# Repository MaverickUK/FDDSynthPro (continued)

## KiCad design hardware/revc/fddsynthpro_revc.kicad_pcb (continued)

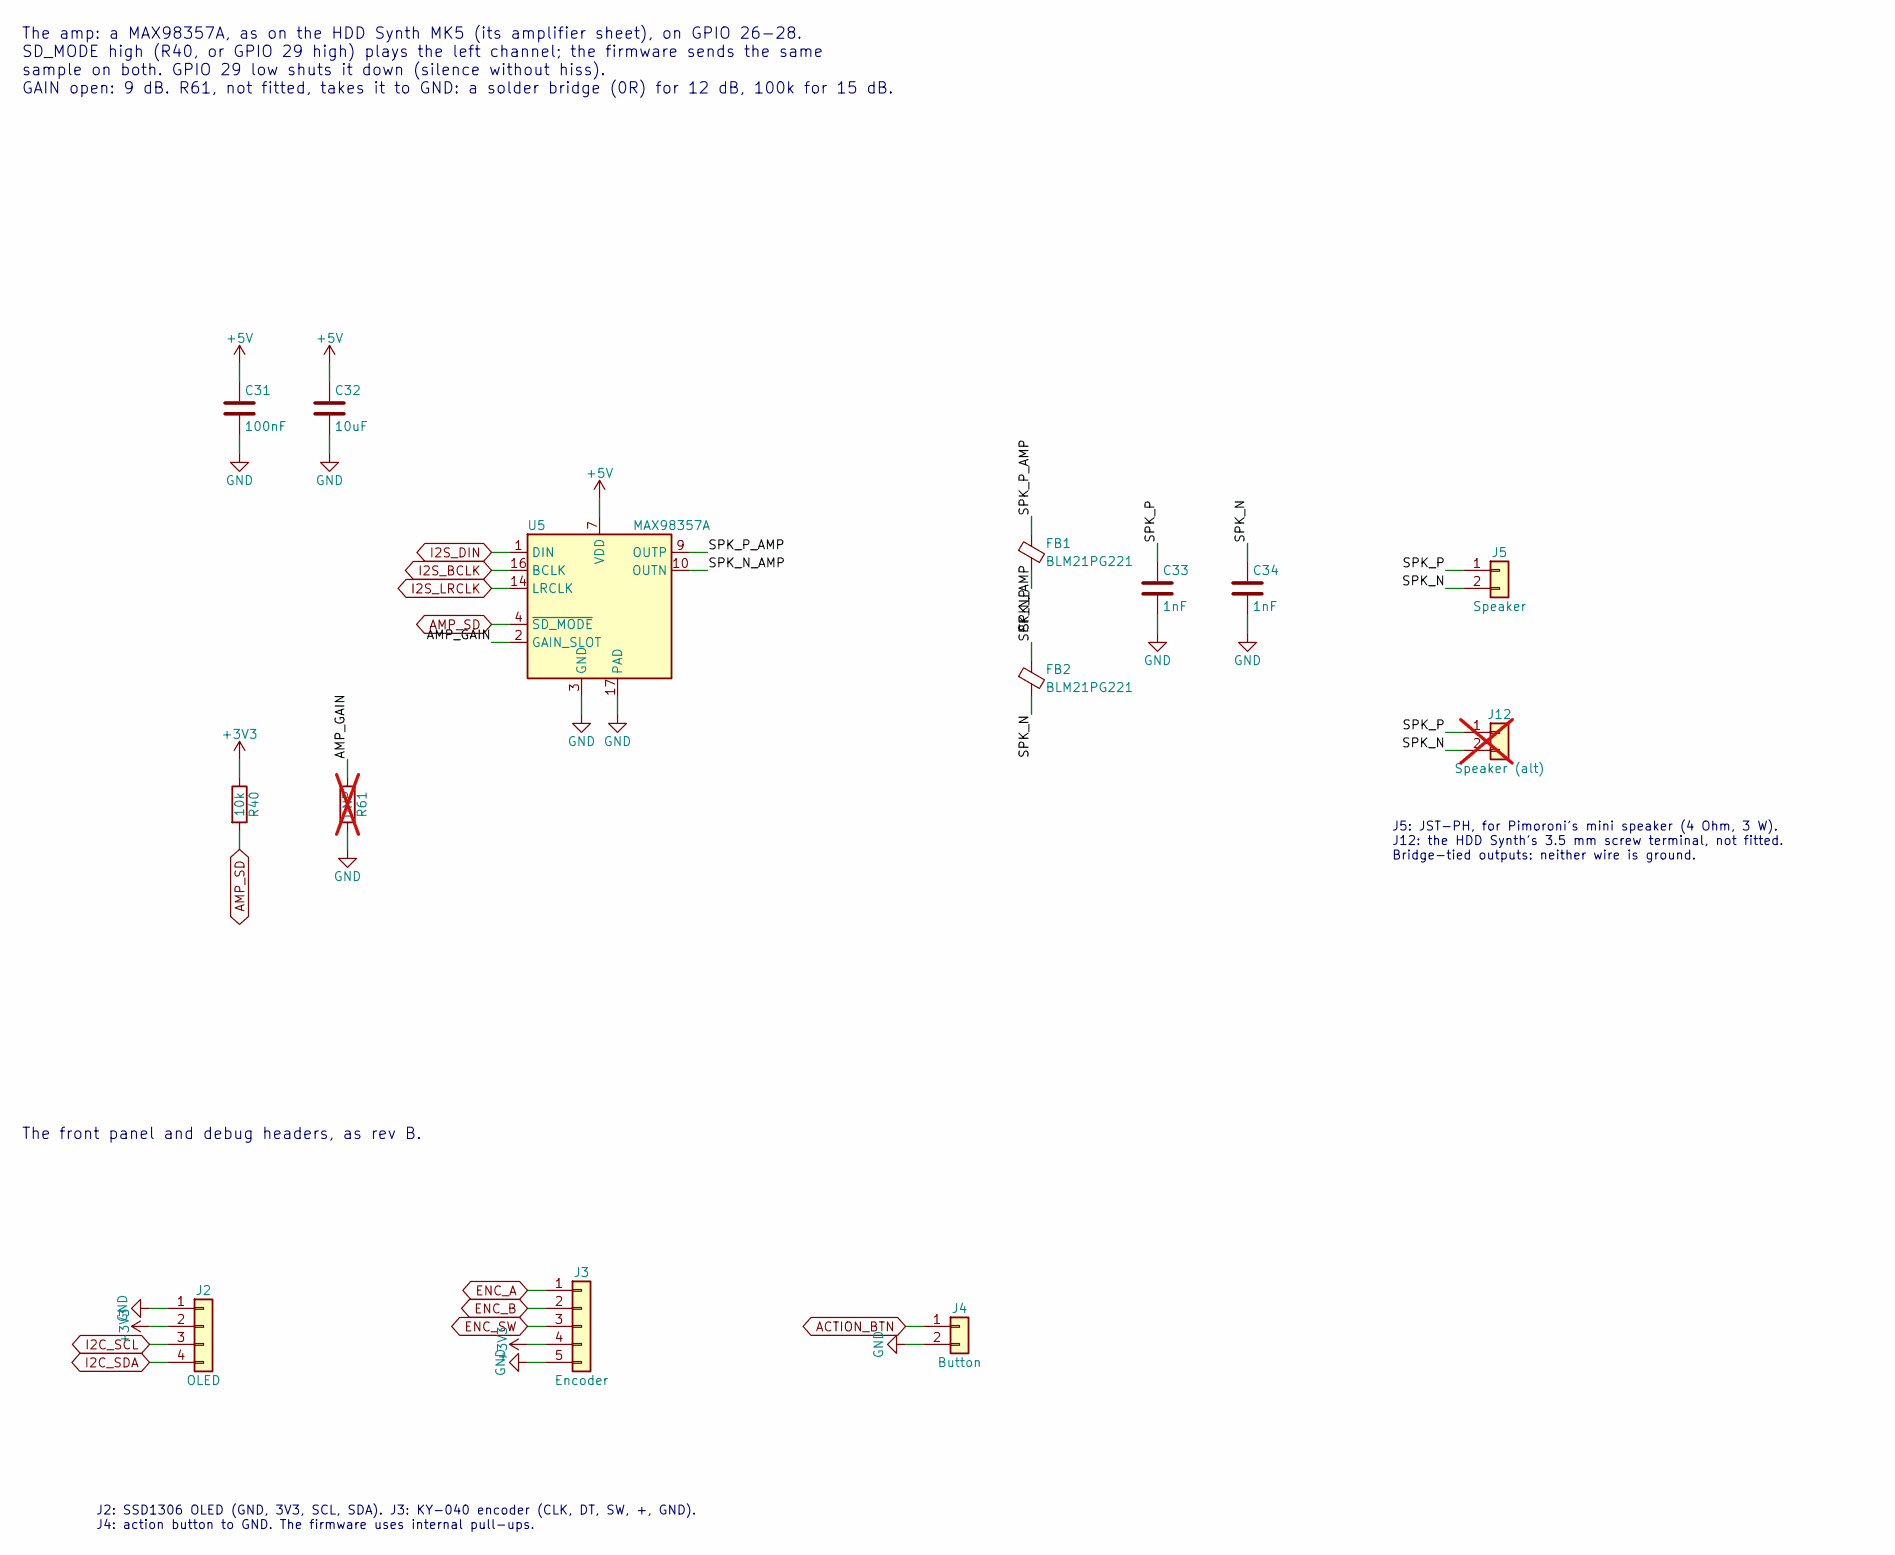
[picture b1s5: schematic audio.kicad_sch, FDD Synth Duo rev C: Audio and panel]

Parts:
C31: 100nF; C_0402_1005Metric; LCSC Part Number C1525
C32: 10uF; C_0805_2012Metric; LCSC Part Number C15850
C33, C34: 1nF; C_0603_1608Metric; LCSC Part Number C1588
FB1, FB2: BLM21PG221; L_0805_2012Metric; LCSC Part Number C85840
J2: OLED; PinHeader_1x04_P2.54mm_Vertical; LCSC Part Number C124378
J3: Encoder; PinHeader_1x05_P2.54mm_Vertical; LCSC Part Number C124379
J4: Button; PinHeader_1x02_P2.54mm_Vertical; LCSC Part Number C124375
J5: Speaker; JST_PH_B2B-PH-K_1x02_P2.00mm_Vertical; MPN JST B2B-PH-K-S; LCSC Part Number C131337
J12: Speaker (alt); TerminalBlock_Phoenix_PT-1,5-2-3.5-H_1x02_P3.50mm_Horizontal; MPN KF350-3.5-2P; LCSC Part Number C474892; not fitted
R40: 10k; R_0402_1005Metric; LCSC Part Number C25744
R61: DNP; R_0402_1005Metric; not fitted
U5: MAX98357A; TQFN-16-1EP_3x3mm_P0.5mm_EP1.23x1.23mm_ThermalVias; LCSC Part Number C910544

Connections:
+3V3: J2.2, J3.4, R40.1; also elsewhere on the board
+5V: C31.1, C32.1, U5.7 (VDD), U5.8 (VDD); also elsewhere on the board
/Audio and panel/AMP_GAIN: R61.1, U5.2 (GAIN_SLOT)
/Audio and panel/SPK_N: C34.1, FB2.2, J5.2, J12.2
/Audio and panel/SPK_N_AMP: FB2.1, U5.10 (OUTN)
/Audio and panel/SPK_P: C33.1, FB1.2, J5.1, J12.1
/Audio and panel/SPK_P_AMP: FB1.1, U5.9 (OUTP)
ACTION_BTN: J4.1; also elsewhere on the board
AMP_SD: R40.2, U5.4 (~SD_MODE); also elsewhere on the board
ENC_A: J3.1; also elsewhere on the board
ENC_B: J3.2; also elsewhere on the board
ENC_SW: J3.3; also elsewhere on the board
GND: C31.2, C32.2, C33.2, C34.2, J2.1, J3.5, J4.2, R61.2, U5.3 (GND), U5.11 (GND), U5.15 (GND), U5.17 (PAD); also elsewhere on the board
I2C_SCL: J2.3; also elsewhere on the board
I2C_SDA: J2.4; also elsewhere on the board
I2S_BCLK: U5.16 (BCLK); also elsewhere on the board
I2S_DIN: U5.1 (DIN); also elsewhere on the board
I2S_LRCLK: U5.14 (LRCLK); also elsewhere on the board

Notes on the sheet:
The amp: a MAX98357A, as on the HDD Synth MK5 (its amplifier sheet), on GPIO 26-28. SD_MODE high (R40, or GPIO 29 high) plays the left channel; the firmware sends the same sample on both. GPIO 29 low shuts it down (silence without hiss). GAIN open: 9 dB. R61, not fitted, takes it to GND: a solder b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
J5: JST-PH, for Pimoroni's mini speaker (4 Ohm, 3 W). J12: the HDD Synth's 3.5 mm screw terminal, not fitted. Bridge-tied outputs: neither wire is ground.
The front panel and debug headers, as rev B.
J2: SSD1306 OLED (GND, 3V3, SCL, SDA). J3: KY-040 encoder (CLK, DT, SW, +, GND). J4: action button to GND. The firmware uses internal pull-ups.

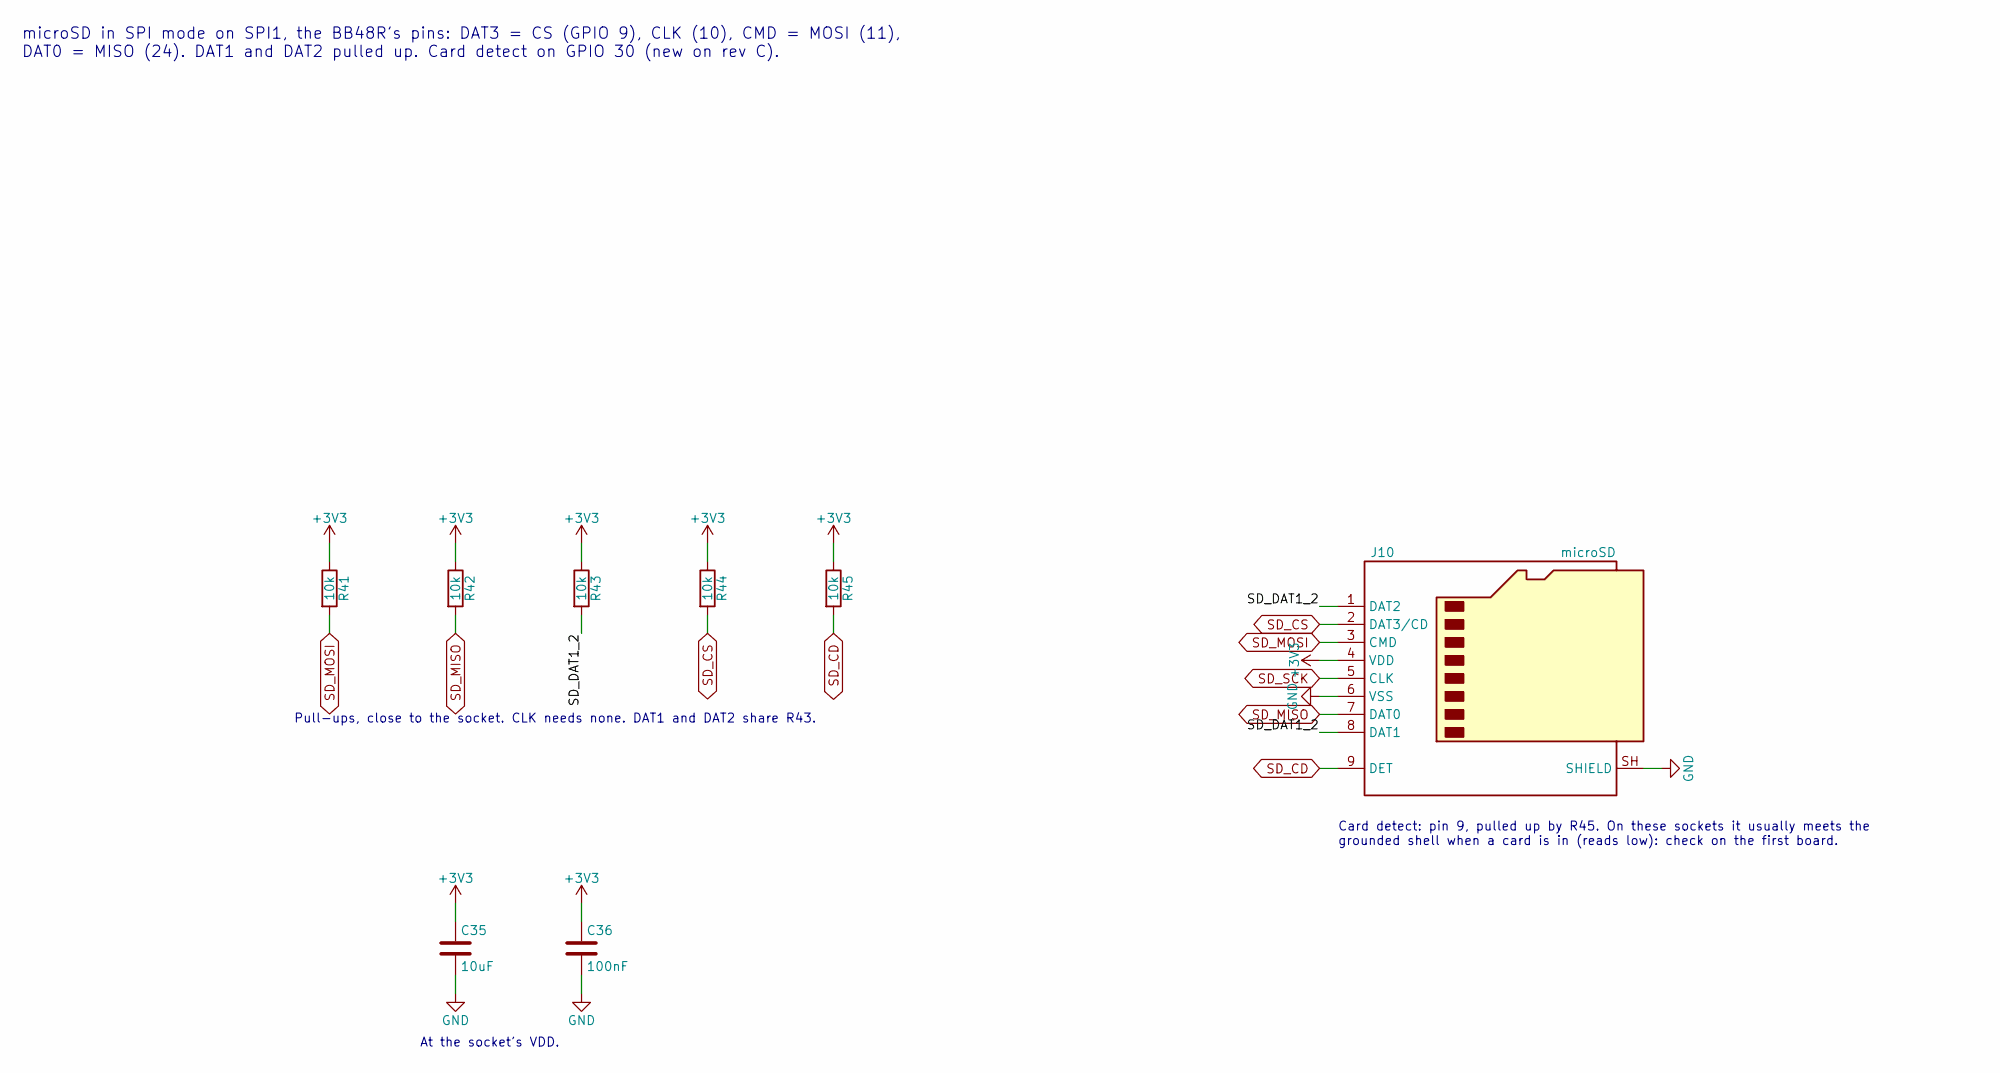
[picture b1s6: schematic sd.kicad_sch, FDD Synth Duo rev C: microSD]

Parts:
C35: 10uF; C_0805_2012Metric; LCSC Part Number C15850
C36: 100nF; C_0402_1005Metric; LCSC Part Number C1525
J10: microSD; microSD_TF-PUSH; MPN TF PUSH (generic push-push); LCSC Part Number C393941
R41, R42, R43, R44, R45: 10k; R_0402_1005Metric; LCSC Part Number C25744

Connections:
+3V3: C35.1, C36.1, J10.4 (VDD), R41.1, R42.1, R43.1, R44.1, R45.1; also elsewhere on the board
/microSD/SD_DAT1_2: J10.1 (DAT2), J10.8 (DAT1), R43.2
GND: C35.2, C36.2, J10.6 (VSS), J10.SH (SHIELD); also elsewhere on the board
SD_CD: J10.9 (DET), R45.2; also elsewhere on the board
SD_CS: J10.2 (DAT3/CD), R44.2; also elsewhere on the board
SD_MISO: J10.7 (DAT0), R42.2; also elsewhere on the board
SD_MOSI: J10.3 (CMD), R41.2; also elsewhere on the board
SD_SCK: J10.5 (CLK); also elsewhere on the board

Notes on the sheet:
microSD in SPI mode on SPI1, the BB48R's pins: DAT3 = CS (GPIO 9), CLK (10), CMD = MOSI (11), DAT0 = MISO (24). DAT1 and DAT2 pulled up. Card detect on GPIO 30 (new on rev C).
Card detect: pin 9, pulled up by R45. On these sockets it usually meets the grounded shell when a card is in (reads low): check on the first board.
Pull-ups, close to the socket. CLK needs none. DAT1 and DAT2 share R43.
At the socket's VDD.

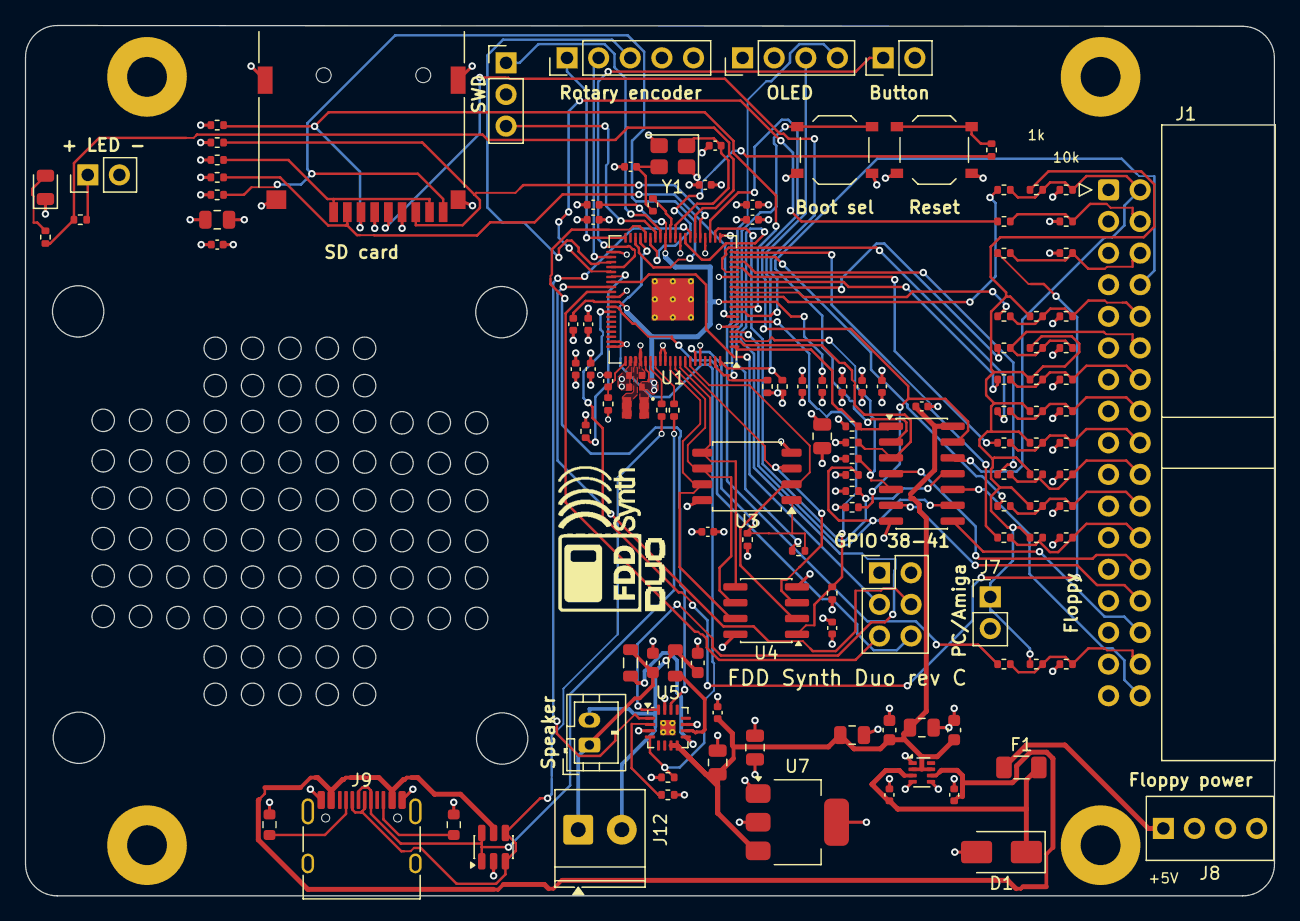
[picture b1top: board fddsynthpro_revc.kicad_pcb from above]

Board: 4 copper layers, 100.3 x 69.9 mm, 134 parts (1 on the bottom side), 95 nets.

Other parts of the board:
LOGO1: FDDSynthDuo_Logo
LOGO2: DontCopyThatFloppy

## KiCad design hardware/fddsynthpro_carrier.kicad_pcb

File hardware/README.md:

# FDD Synth Duo carrier board

A KiCad 10 project for the board the Olimex RP2350-PICO2-BB48R plugs onto: the SN7407, the floppy header, the input pull-ups, and headers for the front panel and the amp. It's the circuit in [docs/wiring.md](../docs/wiring.md), with the pin map in [src/config.h](../src/config.h).

**Rev B** has the HDD Synth MK5's outline, mounting holes and speaker grille, so it fits the same case. It's built for JLCPCB assembly: they fit everything but the BB48R, which is marked DNP (do not populate) and plugged in by hand.

## The board

- **The outline**, 100.3 × 69.9 mm, is copied from the HDD Synth MK5's own PCB ([mk5_outline.py](mk5_outline.py)). That includes its speaker grille, the four 4.1 mm speaker-mounting holes, and the four M3 mounting holes (plated and grounded, as on the MK5). No copper goes under the speaker.
- **The speaker** is Pimoroni's mini speaker (4 Ω, 3 W, JST-PH): 40 × 40 × 20 mm, M2.5 holes 32.5 mm apart. On the MK5's holes (34 mm apart, 4.1 mm across) it covers x 1.3–41.3 mm; the nearest part (the header column) starts 2.3 mm beyond its frame. The MK5's holes are 0.75 mm wider-spaced than the speaker's on each side, which an M2.5 screw in a 4.1 mm hole just takes.
- **The BB48R stands upright, turned round:** its USB-C socket is at the bottom edge and its microSD slot (on its underside) at the top edge. Turned this way, its EXT1 row, which carries every floppy signal, faces J1, and its EXT2 row, with the amp and encoder pins, faces the headers. The pin map is unchanged. The case may need openings for both; the HDD Synth's USB-C sits on the right edge instead.
- **J1, the floppy box header,** is on the right, between the right-hand mounting holes, turned round so its signal row faces the BB48R.
- **The pull-ups:** the twenty 0402 resistors stand between the BB48R and J1, one 10 kΩ and one 1 kΩ on each input's row. Each input runs straight along its row through both, and their other ends drop through vias to two buses on the underside.
- **The SN7407 (U2)** and its 100 nF capacitor sit below the pull-ups, beside GP4–7, its inputs.
- **The headers** form one column on the left, between the speaker and the BB48R, labelled pin by pin and titled beside each group.
- **Tracks:** 0.3 mm everywhere (ground, 3.3 V and VBUS all cross under the BB48R, between its pins, where nothing wider fits), 0.2 mm clearance, 0.6/0.3 mm vias, and ground poured on both sides. A 0.3 mm track carries about 1 A.

## The circuit

| Ref | Part | LCSC | Fitted by | Notes |
|---|---|---|---|---|
| U1 | Olimex RP2350-PICO2-BB48R | — | You (DNP) | Two 1×27 female headers are best: they give the microSD card room underneath and let you swap the board |
| U2 | SN7407DR, SOIC-14 | C40481 | JLCPCB | The five outputs: GPIO → A, Y → floppy header. Powered from VBUS; the sixth gate's input is tied to GND (see the pin 2 rework below) |
| C1 | 100 nF, 0603 | C14663 | JLCPCB | U2's decoupling |
| R1–R10 | 10 kΩ, 0402 | C25744 | JLCPCB | Pull-ups on the ten inputs to 3.3 V: right for the FeatherWing host |
| R11–R20 | 1 kΩ, 0402 | C11702 | JLCPCB | Pull-ups to PC_TERM, which J7 joins to 3.3 V |
| J1 | 2×17 box header, straight | C9042 | JLCPCB | The floppy cable. Odd pins to ground; 4 and 6 unconnected |
| J2 | 1×4 header: GND, 3V3, SCL, SDA | C124378 | JLCPCB | SSD1306 OLED. The BB48R's own Qwiic socket carries the same I2C1 pins |
| J3 | 1×5 header: CLK, DT, SW, +, GND | C124379 | JLCPCB | Rotary encoder. A KY-040 module plugs straight in |
| J4 | 1×2 header | C124375 | JLCPCB | The action button, to GND |
| J5 | 1×7 header: LRC, BCLK, DIN, GAIN, SD, GND, Vin | C492406 | JLCPCB | Adafruit MAX98357A, in its own pin order. GAIN and SD unconnected |
| J6 | 1×3 header: TX, RX, GND | C124376 | JLCPCB | Debug UART on GP0/GP1 |
| J7 | 1×2 header and a jumper | C124375 | JLCPCB (the jumper cap: you) | **The termination switch:** off for the FeatherWing host (10 kΩ); on for a real PC (the 1 kΩ in parallel: 909 Ω) |

The BB48R's own pins are left alone: GP8 (PSRAM select), GP9–11 and GP24 (the microSD slot), and GP25 (the LED).

**Rework for Shugart and Amiga hosts:** rev B only reads floppy pin 2 (a PC's density select). Shugart and Amiga hosts want the drive to drive it, with DISK CHANGE. Lift U2 pin 13 from ground and wire it to GP23 (EXT1-27), wire U2 pin 12 to J1 pin 2, and set `pin02=chg` ([docs/wiring.md](../docs/wiring.md#pin-2-for-shugart-and-amiga-hosts-a-rework)). A rev C should route the sixth gate that way from the start.

Rev A had a socketed DIP SN7407 and solder jumpers (JP1–JP5) to bypass it for the `direct` builds. A soldered SOIC can't be taken out, so rev B always has its SN7407. The `direct` builds remain for hand-wired rigs.

## Ordering from JLCPCB

`hardware/build.sh` writes everything:

- `fddsynthpro_carrier_fab.zip`: the Gerbers and drill files. Upload it as it is: two layers, 1.6 mm, HASL or ENIG.
- `jlc/bom.csv` and `jlc/positions.csv`: the assembly BOM and placement (CPL) in JLCPCB's format, without U1 (DNP). KiCad's Fabrication Toolkit plugin writes its own set to `production/` (with "Exclude DNP" on, in `fabrication-toolkit-options.json`); either set works. Choose top-side assembly. J1–J7 are through-hole, so they need Standard PCBA rather than Economic.

Each part's LCSC number is in a field named **LCSC Part Number**, as on the HDD Synth, so KiCad's Fabrication Toolkit plugin fills its BOM from the schematic too; it also leaves U1 out when "Exclude DNP" is set. The pin headers are Ckmtw's `B-2100S0xP-A110`, as on the HDD Synth; Ckmtw makes no 1×7, so J5 is XFCN's `PZ254V-11-07P`.

**Before paying, check JLCPCB's placement preview.** Their footprints don't always share KiCad's zero angle, SOICs especially, so make sure U2's pin-1 dot matches the board's marking. Rotate it in the preview if not.

**Extended parts:** U2, J1 and the five different pin headers are JLCPCB "extended" parts, and JLCPCB charges a one-off loading fee for each extended part in an order. Fitting the 1×N headers yourself saves five of those fees: delete their lines from the BOM before uploading.

**Stock:** U2's stock was low (under 100) when checked. If it's out, TI's SN74LS07 is a hex open-collector buffer with the same pinout; check its datasheet's output sink current against the host's termination before swapping.

## Changing it

The schematic, board and assembly files are generated, so edit the pin map in `make_schematic.py` (and the placement in `make_pcb.py`) and rebuild:

```sh
hardware/build.sh                                             # expect 0 ERC and 0 DRC violations; takes about 2 minutes
cd host && .venv/bin/pytest tests/test_carrier_schematic.py   # the netlist against src/config.h
```

| File | What it is |
|---|---|
| `fddsynthpro_carrier.kicad_pro` | The project: open this in KiCad |
| `fddsynthpro_carrier.kicad_sch`, `.kicad_pcb` | The schematic and board (generated) |
| `fddsynthpro_carrier.kicad_dru` | One design rule: a ground thermal relief may have a single spoke (ground is also tracked) |
| `FDDSynthPro.kicad_sym`, `FDDSynthPro.pretty/` | The BB48R's symbol and footprint (measured from Olimex's own PCB) |
| `make_schematic.py`, `sexp.py` | The schematic's generator |
| `make_pcb.py` | The board's generator: placement, a rip-up-and-reroute maze router, the pours, the logo (about a minute) |
| `mk5_outline.py` | The HDD Synth MK5's outline and holes |
| `make_jlc.py` | Writes JLCPCB's BOM and placement files to `jlc/` |
| `build.sh` | Rebuilds it all, checks it (ERC, DRC with schematic parity) and writes the fabrication files |

`make_pcb.py` needs KiCad's own Python, for `pcbnew`; `build.sh` finds it in the macOS app (set `KICAD_PYTHON` elsewhere). The schematic test exports the netlist with `kicad-cli` and checks every connection against `src/config.h`; it skips where `kicad-cli` isn't installed (CI).

Editing the files by hand in KiCad works too, but the next run of the generators overwrites them. Once you start making changes by hand, stop running `build.sh`: the KiCad files become the source, and the test still checks the schematic against `config.h`.

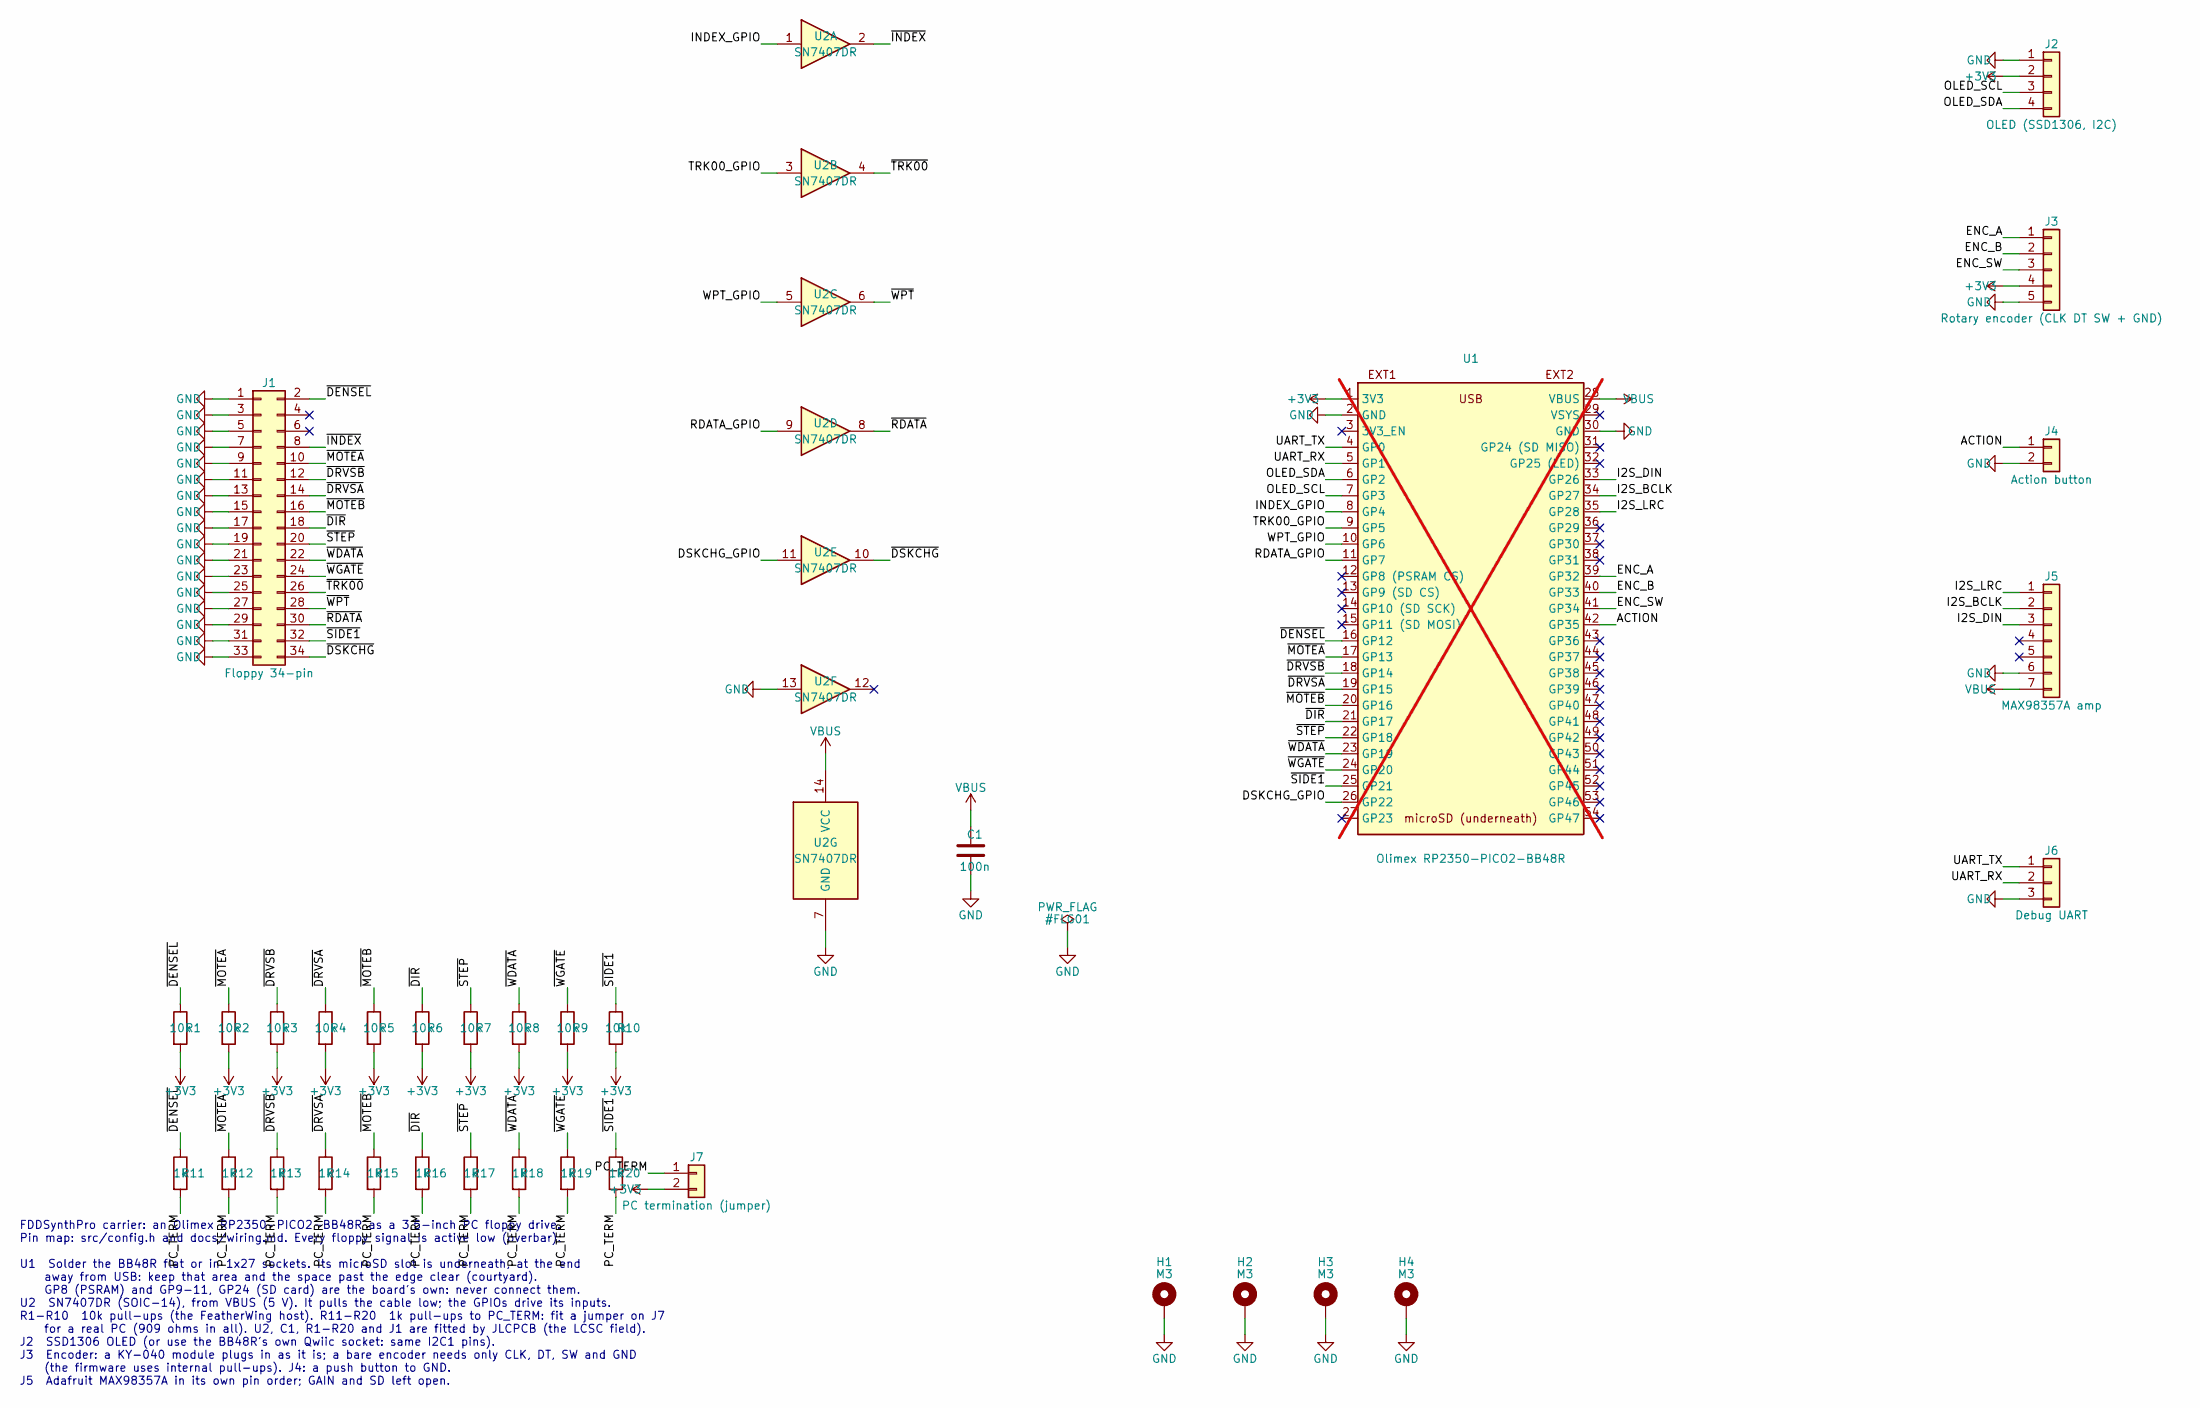
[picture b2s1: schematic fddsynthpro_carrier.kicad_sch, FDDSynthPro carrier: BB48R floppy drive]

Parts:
C1: 100n; C_0603_1608Metric; LCSC Part Number C14663
H1, H2, H3, H4: M3; MountingHole_3.2mm_M3_Pad
J1: Floppy 34-pin; IDC-Header_2x17_P2.54mm_Vertical; LCSC Part Number C9042
J2: OLED (SSD1306, I2C); PinHeader_1x04_P2.54mm_Vertical; LCSC Part Number C124378
J3: Rotary encoder (CLK DT SW + GND); PinHeader_1x05_P2.54mm_Vertical; LCSC Part Number C124379
J4: Action button; PinHeader_1x02_P2.54mm_Vertical; LCSC Part Number C124375
J5: MAX98357A amp; PinHeader_1x07_P2.54mm_Vertical; LCSC Part Number C492406
J6: Debug UART; PinHeader_1x03_P2.54mm_Vertical; LCSC Part Number C124376
J7: PC termination (jumper); PinHeader_1x02_P2.54mm_Vertical; LCSC Part Number C124375
R1, R2, R3, R4, R5, R6, R7, R8, R9, R10: 10k; R_0402_1005Metric; LCSC Part Number C25744
R11, R12, R13, R14, R15, R16, R17, R18, R19, R20: 1k; R_0402_1005Metric; LCSC Part Number C11702
U1: Olimex RP2350-PICO2-BB48R; Olimex_RP2350-PICO2-BB48; not fitted
U2: SN7407DR; SOIC-14_3.9x8.7mm_P1.27mm; LCSC Part Number C40481

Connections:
+3V3: J2.2, J3.4, J7.2, R1.2, R2.2, R3.2, R4.2, R5.2, R6.2, R7.2, R8.2, R9.2, R10.2, U1.1 (3V3)
/ACTION: J4.1, U1.42 (GP35)
/DSKCHG_GPIO: U1.26 (GP22), U2.11
/ENC_A: J3.1, U1.39 (GP32)
/ENC_B: J3.2, U1.40 (GP33)
/ENC_SW: J3.3, U1.41 (GP34)
/I2S_BCLK: J5.2, U1.34 (GP27)
/I2S_DIN: J5.3, U1.33 (GP26)
/I2S_LRC: J5.1, U1.35 (GP28)
/INDEX_GPIO: U1.8 (GP4), U2.1
/OLED_SCL: J2.3, U1.7 (GP3)
/OLED_SDA: J2.4, U1.6 (GP2)
/PC_TERM: J7.1, R11.2, R12.2, R13.2, R14.2, R15.2, R16.2, R17.2, R18.2, R19.2, R20.2
/RDATA_GPIO: U1.11 (GP7), U2.9
/TRK00_GPIO: U1.9 (GP5), U2.3
/UART_RX: J6.2, U1.5 (GP1)
/UART_TX: J6.1, U1.4 (GP0)
/WPT_GPIO: U1.10 (GP6), U2.5
/~DENSEL: J1.2, R1.1, R11.1, U1.16 (GP12)
/~DIR: J1.18, R6.1, R16.1, U1.21 (GP17)
/~DRVSA: J1.14, R4.1, R14.1, U1.19 (GP15)
/~DRVSB: J1.12, R3.1, R13.1, U1.18 (GP14)
/~DSKCHG: J1.34, U2.10
/~INDEX: J1.8, U2.2
/~MOTEA: J1.10, R2.1, R12.1, U1.17 (GP13)
/~MOTEB: J1.16, R5.1, R15.1, U1.20 (GP16)
/~RDATA: J1.30, U2.8
/~SIDE1: J1.32, R10.1, R20.1, U1.25 (GP21)
/~STEP: J1.20, R7.1, R17.1, U1.22 (GP18)
/~TRK00: J1.26, U2.4
/~WDATA: J1.22, R8.1, R18.1, U1.23 (GP19)
/~WGATE: J1.24, R9.1, R19.1, U1.24 (GP20)
/~WPT: J1.28, U2.6
GND: C1.2, H1.1, H2.1, H3.1, H4.1, J1.1, J1.3, J1.5, J1.7, J1.9, J1.11, J1.13, J1.15, J1.17, J1.19, J1.21, J1.23, J1.25, J1.27, J1.29, J1.31, J1.33, J2.1, J3.5, J4.2, J5.6, J6.3, U1.2 (GND), U1.30 (GND), U2.7 (GND), U2.13
VBUS: C1.1, J5.7, U1.28 (VBUS), U2.14 (VCC)

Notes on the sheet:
FDDSynthPro carrier: an Olimex RP2350-PICO2-BB48R as a 3.5-inch PC floppy drive. Pin map: src/config.h and docs/wiring.md. Every floppy signal is active low (overbar). U1 Solder the BB48R flat or in 1x27 sockets. Its microSD slot is underneath, at the end away from USB: keep that area and the space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

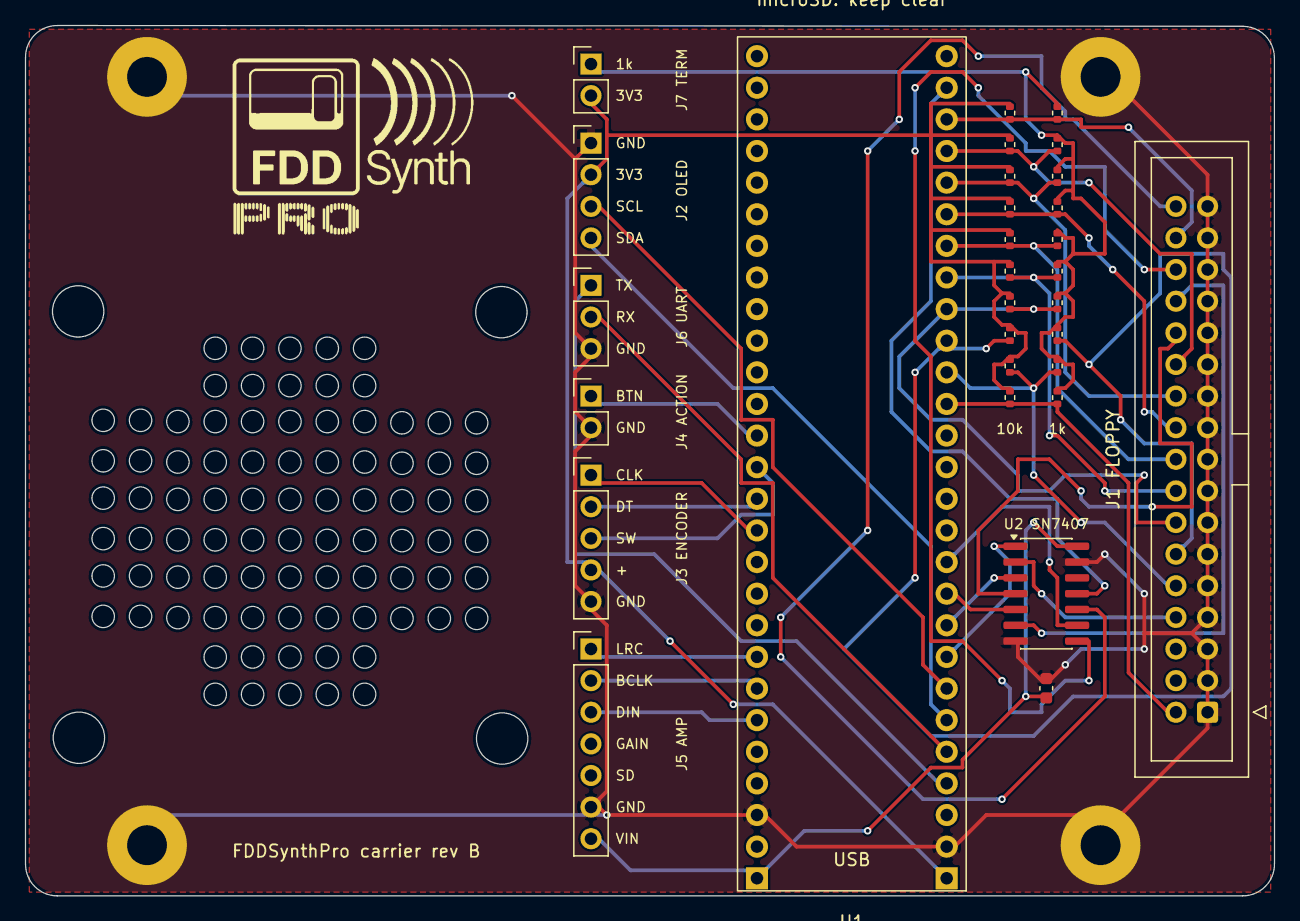
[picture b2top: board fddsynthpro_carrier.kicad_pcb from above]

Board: 2 copper layers, 100.3 x 69.9 mm, 34 parts (0 on the bottom side), 35 nets.

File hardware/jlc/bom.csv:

Comment,Designator,Footprint,LCSC Part #
100n,C1,C_0603_1608Metric,C14663
Floppy 34-pin,J1,IDC-Header_2x17_P2.54mm_Vertical,C9042
"OLED (SSD1306, I2C)",J2,PinHeader_1x04_P2.54mm_Vertical,C124378
Rotary encoder (CLK DT SW + GND),J3,PinHeader_1x05_P2.54mm_Vertical,C124379
Action button / PC termination (jumper),"J4,J7",PinHeader_1x02_P2.54mm_Vertical,C124375
MAX98357A amp,J5,PinHeader_1x07_P2.54mm_Vertical,C492406
Debug UART,J6,PinHeader_1x03_P2.54mm_Vertical,C124376
10k,"R1,R2,R3,R4,R5,R6,R7,R8,R9,R10",R_0402_1005Metric,C25744
1k,"R11,R12,R13,R14,R15,R16,R17,R18,R19,R20",R_0402_1005Metric,C11702
SN7407DR,U2,SOIC-14_3.9x8.7mm_P1.27mm,C40481

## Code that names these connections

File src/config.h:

// Pin map and sizes. Pure constants, so host tests can include it.
// docs/wiring.md maps each pin to the floppy header.
#pragma once

#include <cstddef>
#include <cstdint>

namespace cfg {

// The pin map is for the BB48R, the BB48 with PSRAM and a microSD slot
// (docs/wiring.md). The floppy interface uses GPIO 4-7 and 12-22, all inside
// one PIO block's GPIO 0-31 window. Avoided on purpose:
//   GPIO 0-3  the BB48 pulls GPIO 2/3 up to 3.3 V through 2.2k (R17/R18,
//             UEXT/Qwiic I2C); GPIO 0/1 stay free for a UART if needed.
//   GPIO 8    the PSRAM's chip select (the board's own wiring).
//   GPIO 9-11, 24  the microSD slot (the board's own wiring).
//   GPIO 25   the on-board LED (2.2k + LED to GND).
//
// Every floppy signal is active low. Inputs come from the host's drivers and
// are pulled up to 3.3 V by resistors on our side (the drive end terminates
// the cable: 10k with the FeatherWing host, 1k for a PC). Outputs go through
// an SN7407 open-collector buffer: GPIO low asserts the line, GPIO high
// releases it.

// Inputs (host -> drive), on consecutive pins so one read captures them all.
constexpr unsigned PIN_DENSEL = 12;  // floppy pin 2: density select
constexpr unsigned PIN_MOTEA = 13;   // floppy pin 10: motor enable A
constexpr unsigned PIN_DRVSB = 14;   // floppy pin 12: drive select B (a PC drive's own select)
constexpr unsigned PIN_DRVSA = 15;   // floppy pin 14: drive select A
constexpr unsigned PIN_MOTEB = 16;   // floppy pin 16: motor enable B (a PC drive's own motor)
constexpr unsigned PIN_DIR = 17;     // floppy pin 18: asserted = step in (towards higher cylinders)
constexpr unsigned PIN_STEP = 18;    // floppy pin 20: one step per assertion
constexpr unsigned PIN_WDATA = 19;   // floppy pin 22: write data (slice 5)
constexpr unsigned PIN_WGATE = 20;   // floppy pin 24: write gate
constexpr unsigned PIN_SIDE1 = 21;   // floppy pin 32: asserted = head 1

// Outputs (drive -> host), through the SN7407. Four below the PSRAM and SD
// pins, two after the inputs.
constexpr unsigned PIN_INDEX = 4;    // floppy pin 8: once per revolution
constexpr unsigned PIN_TRK00 = 5;    // floppy pin 26: head on cylinder 0
constexpr unsigned PIN_WPT = 6;      // floppy pin 28: write protected
constexpr unsigned PIN_RDATA = 7;    // floppy pin 30: read data (flux pulses)
constexpr unsigned PIN_DSKCHG = 22;  // floppy pin 34: disk changed (PC), or READY (Shugart, Amiga)
// Floppy pin 2 as an output: DISK CHANGE for Shugart and Amiga hosts
// (/CHNG), which a PC uses as its density select instead. Not on the rev B
// carrier as built: it needs a rework, the SN7407's spare gate (input pin
// 13 lifted from ground to GP23, output pin 12 to floppy pin 2;
// docs/wiring.md). Released unless `pin02=chg` is set (docs/config.md).
constexpr unsigned PIN_CHNG = 23;
constexpr unsigned OUTPUT_PINS[] = {PIN_INDEX, PIN_TRK00, PIN_WPT, PIN_RDATA, PIN_DSKCHG, PIN_CHNG};

// How the outputs reach the cable, set per build in platformio.ini:
//   0  through the SN7407 (the default): the GPIOs drive its inputs high and
//      low, and it pulls the cable low.
//   1  wired straight to the header, for bring-up with the FeatherWing host
//      before the SN7407 arrives. Each pin works as open drain: its level is
//      always low, and asserting a line enables the output; releasing it
//      makes the pin an input again, and the host's pull-up takes the line
//      to 5 V, which the RP2350's pins tolerate while it is powered. Never
//      with a real PC: its termination can need more current than a GPIO
//      can sink, and nothing would protect the RP2350 from the cable.
#ifndef FDD_OUTPUTS_OPEN_DRAIN
#define FDD_OUTPUTS_OPEN_DRAIN 0
#endif
constexpr bool OUTPUTS_OPEN_DRAIN = FDD_OUTPUTS_OPEN_DRAIN;

constexpr unsigned PIN_BOARD_LED = 25;  // on-board LED, not a floppy line

// The BB48R's own microSD slot and PSRAM, fixed by the board. Only DAT0 and
// DAT3 of the card are wired, so it runs in SPI mode on SPI1 (the variant
// file's SPI1 pins). The board has the card's pull-ups.
constexpr unsigned PIN_PSRAM_CS = 8;  // used by the core, never by us
constexpr unsigned PIN_SD_CS = 9;     // the card's DAT3
constexpr unsigned PIN_SD_SCK = 10;   // CLK
constexpr unsigned PIN_SD_MOSI = 11;  // CMD
constexpr unsigned PIN_SD_MISO = 24;  // DAT0
// 25 MHz, the SD spec's default speed: a 9 KB track in about 3.5 ms. Too
// slow to read tracks as the head moves (the settle time is 15 ms), so the
// drive serves each disk from a copy in PSRAM (image_cache.h), filled
// before the disk goes in: 160 tracks, about 0.6 s.
constexpr uint32_t SD_SPI_MHZ = 25;

// The image cache: one whole image in PSRAM, per drive. With one drive,
// 4.5 MB: an HD flux image (4 MB of cells, more with long tracks). With
// two, 3 MB each: DD flux images and every sector image but Ensoniq's 5 MB
// SuperDisk. A bigger image's tracks are read from the card (slow seeks).
constexpr size_t IMAGE_CACHE_BYTES = 4608 * 1024;         // one drive
constexpr size_t IMAGE_CACHE_BYTES_EACH = 3 * 1024 * 1024;  // each of two

// Audio: a MAX98357A I2S amp, as on HDDSynth_Native. Below GPIO 32, so the
// I2S PIO program works in the same GPIO 0-31 window as RDATA and WDATA.
constexpr unsigned PIN_I2S_DATA = 26;
constexpr unsigned PIN_I2S_BCLK = 27;  // LRCLK is BCLK + 1 = GPIO 28

// The front panel (drive build, panel.h). The OLED goes on the BB48's own
// Qwiic/UEXT I2C connector (I2C1 on GPIO 2 and 3, already pulled up on the
// board); the encoder and the action button on free pins on EXT2, pulled up
// internally. Each switch connects its pin to ground.
constexpr unsigned PIN_OLED_SDA = 2;        // I2C1, the BB48's Qwiic/UEXT
constexpr unsigned PIN_OLED_SCL = 3;
constexpr unsigned PIN_ENC_A = 32;
constexpr unsigned PIN_ENC_B = 33;
constexpr unsigned PIN_ENC_BUTTON = 34;
constexpr unsigned PIN_ACTION_BUTTON = 35;

// An SSD1306 128x64 at the usual address. A frame is 1,032 bytes on the bus:
// 23 ms at 400 kHz, fed to the I2C FIFO a few bytes per pass of core 0's
// loop, so it never holds anything up.
constexpr uint8_t OLED_I2C_ADDR = 0x3C;
constexpr uint32_t OLED_I2C_HZ = 400000;
constexpr uint32_t OLED_FRAME_MS = 100;       // at most 10 frames a second
constexpr uint32_t HEAD_TRACE_SAMPLE_MS = 50; // the head trace's 128 columns: 6.4 s
constexpr bool ENCODER_REVERSED = false;      // flip if clockwise turns the volume down
constexpr uint32_t BUTTON_DEBOUNCE_MS = 20;
constexpr uint32_t BUTTON_LONG_MS = 1000;     // a long action: eject or insert

// The sample pack lives in RAM (FDD sounds are short), in one allocation
// sized to the pack. Up to 160 KB: the stand-in pack is 152 KB; longer
// samples are cut short.
constexpr size_t SAMPLE_POOL_MAX_BYTES = 160 * 1024;

// The WDATA capture ring: 32 KB is 88 ms of writing at 1.44 MB, the most
// the DMA's ring wrap allows. Core 0 can fall 77 ms behind (the rest is the
// stream's guard): enough for the card holding a write for 50-60 ms, as it
// now and then does, while a PC writes a track's sectors one after another.
// The 16 KB ring (33 ms) lost the write (test_pc_card_stalls).
constexpr size_t CAPTURE_RING_BYTES = 32 * 1024;
constexpr size_t WAV_HEADER_BYTES = 4096;  // a WAV's data must start within this (HDDSynth_Native's rule)

// Mixing on core 0: blocks of 128 frames (5.8 ms at 22.05 kHz), 16 of them
// queued (93 ms). That covers core 0's longest stall between top-ups: an HFE
// head's load (27 ms), and the card, which now and then holds a single write
// or sync for 50-60 ms (seen in the soak; 8 blocks, 46 ms, ran dry). The cost
// is 4 KB of RAM and up to 93 ms between an event and its sound.
constexpr size_t AUDIO_BLOCK_FRAMES = 128;
constexpr size_t AUDIO_BUFFERS = 16;

constexpr unsigned FIRST_INPUT_PIN = PIN_DENSEL;
constexpr unsigned LAST_INPUT_PIN = PIN_SIDE1;
// The span a pin sample covers. It includes the PSRAM and SD pins (8-11),
// which INPUT_MASK and OUTPUT_MASK (fdd_signals.h) leave out.
constexpr unsigned BUS_FIRST_PIN = PIN_INDEX;
constexpr unsigned BUS_LAST_PIN = PIN_CHNG;

// Trace ring between core 1 (producer) and core 0 (consumer):
// 4096 events x 16 bytes = 64 KB.
constexpr size_t TRACE_RING_EVENTS = 4096;

// Steps in the same direction merge into one STEP line unless this far apart.
// Hosts step every 3-6 ms in a seek; a gap this long starts a new seek.
constexpr uint32_t STEP_RUN_GAP_US = 50000;

// Core 0 prints a pending line once the trace has been quiet this long:
// longer than STEP_RUN_GAP_US, so a slow seek still prints as one line.
constexpr unsigned TRACE_FLUSH_MS = 60;

}  // namespace cfg
